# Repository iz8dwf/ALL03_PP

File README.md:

# ALL03_PP
Hi-Lo ALL-03 and MOD-EMUP programmers parallel port interface using the ATF-1502 CPLD.

This is a circuit that allows to use the Hi-Lo ALL-03 (and clones like the
MOD-EMUP) universal programmers/testers via the parallel port interface
using a patched DOSBOX. Original design by Nicola Di Lieto used an EPM7032
CPLD. I've used an ATF1502 CPLD that's still in production.

*** The JTAG port has a non-standard pinout *** 

The 2SB794 PNP darlington transistor can be substituted with a similar PNP
darlington. Using a normal PNP transistor with HFE < 200 makes this switching
voltage inverter misbehave. You can attempt to change the base resistor from
4k7 ohms to 2k2 ohms to make a lower HFE transistor work.

USE AT YOUR OWN RISK! 

PS: I believe a similar approach can be used also for the older CSA-0x ISA card based programmers (HI-LO EPP-0x and ALL-01 for example). Of course the adapter
board must be re-designed and a different patch needs to be created for dosbox. If you are interested (I still have an EPP-04, but I'm not going to use it anymore anytime soon) in such an adapter and want to help, contact me.

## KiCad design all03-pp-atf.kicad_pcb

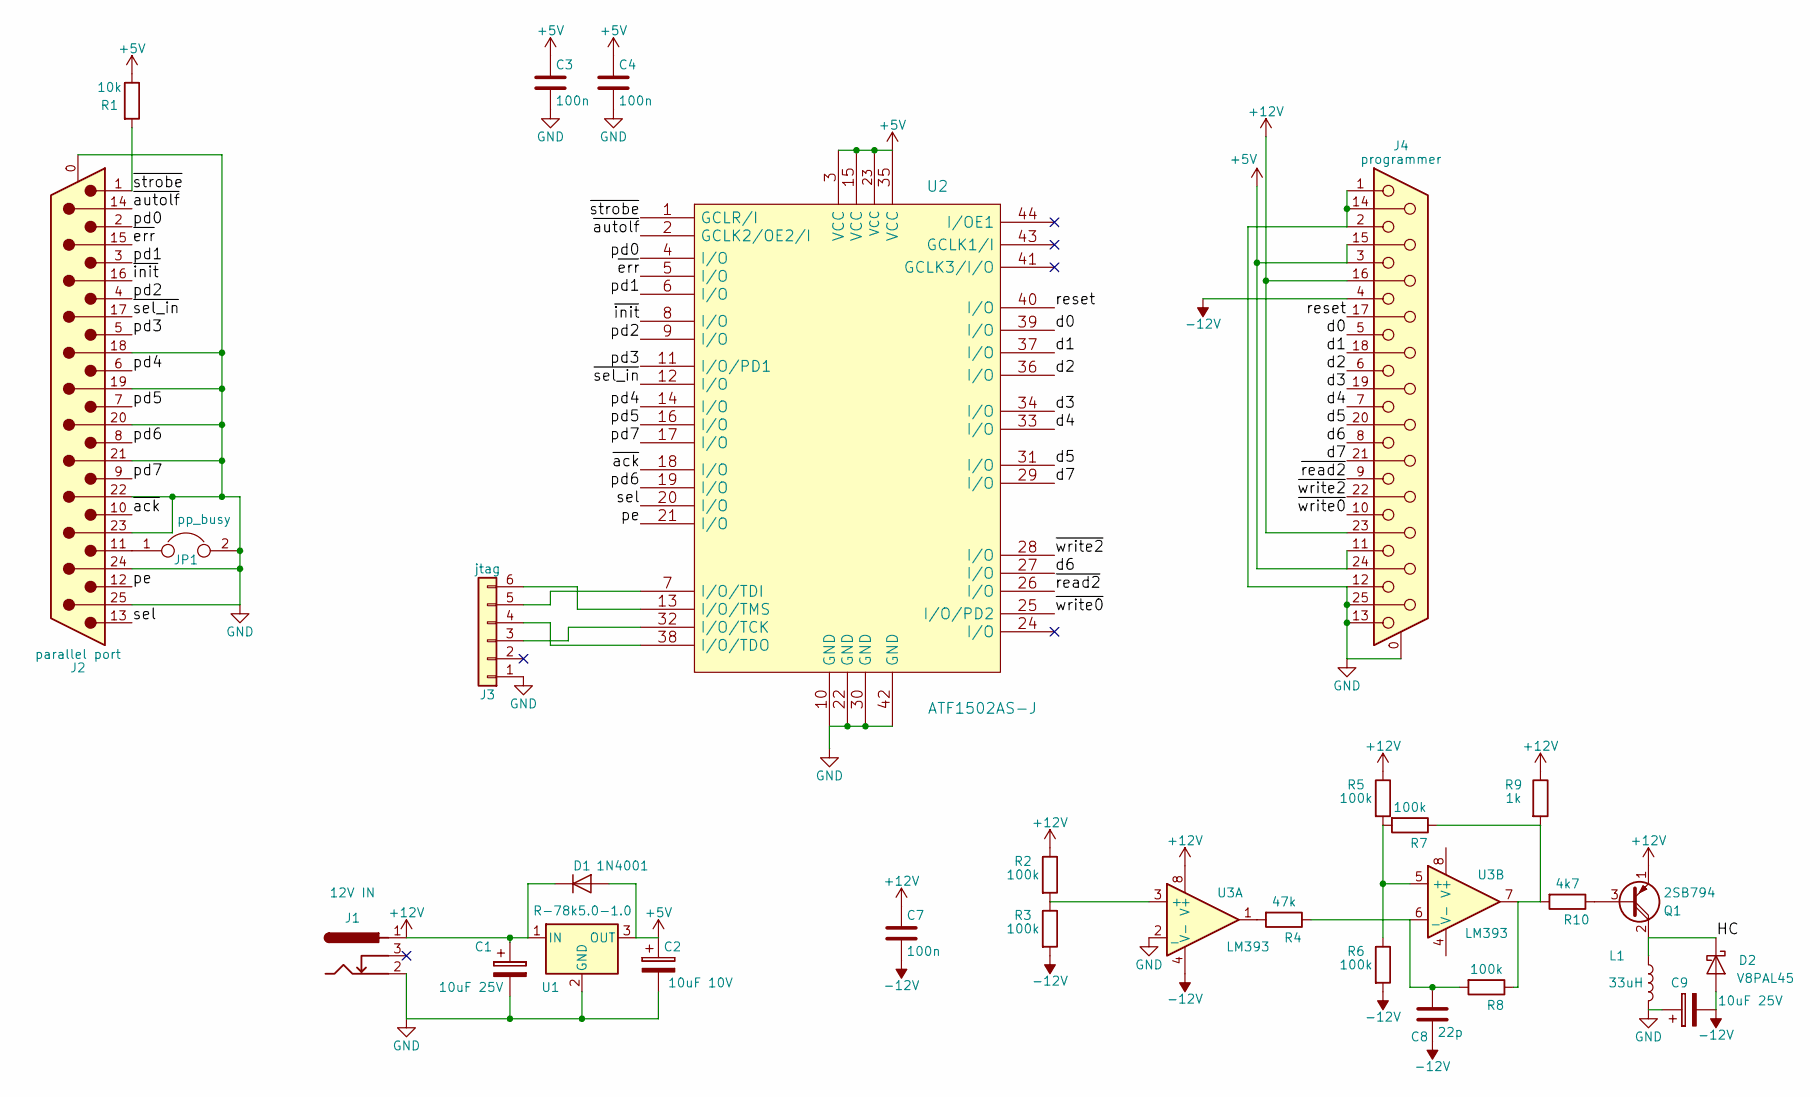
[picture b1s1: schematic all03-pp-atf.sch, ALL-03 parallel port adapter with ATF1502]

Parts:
C1, C9: 10uF 25V; CP_Radial_D5.0mm_P2.50mm
C2: 10uF 10V; CP_Radial_D5.0mm_P2.50mm
C3, C4: 100n; C_0805_HandSoldering
C7: 100n; C_Rect_L7.0mm_W2.5mm_P5.00mm
C8: 22p; C_Disc_D3.8mm_W2.6mm_P2.50mm
D1: 1N4001; D_DO-41_SOD81_P10.16mm_Horizontal
D2: V8PAL45; D_SMA-SMB_Universal_Handsoldering
J1: 12V IN; BARREL_JACK
J2: parallel port; DSUB-25_Male_Horizontal_Pitch2.77x2.84mm_EdgePinOffset4.94m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
J3: jtag; Pin_Header_Straight_1x06_Pitch2.54mm
J4: programmer; DSUB-25_Female_Horizontal_Pitch2.77x2.84mm_EdgePinOffset4.9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
JP1: pp_busy; R_1206_HandSoldering
L1: 33uH; L_Radial_D10.0mm_P5.00mm_Fastron_07P
Q1: 2SB794
R1: 10k; R_0805_HandSoldering
R2, R3, R5, R6, R7, R8: 100k; R_0805_HandSoldering
R4: 47k; R_0805_HandSoldering
R9: 1k; R_0805_HandSoldering
R10: 4k7; R_0805_HandSoldering
U1: R-78k5.0-1.0; TO-220-3_Vertical
U2: ATF1502AS-J; PLCC44
U3: LM393; DIP-8_W7.62mm_Socket

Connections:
+5V: C2.1, C3.1, C4.1, D1.2 (A), J4.3, J4.11, J4.15, J4.24, R1.1, U1.3 (OUT), U2.3 (VCC), U2.15 (VCC), U2.23 (VCC), U2.35 (VCC)
+12V: C1.1, C7.1, D1.1 (K), J1.1, J4.16, J4.23, Q1.1 (E), R2.1, R5.1, R9.1, U1.1 (IN), U3.8 (V+)
-12V: C7.2, C8.2, C9.2, D2.2 (A), J4.4, R3.2, R6.2, U3.4 (V-)
/HC: D2.1 (K), L1.1, Q1.2 (C)
/d0: J4.5, U2.39 (I/O)
/d1: J4.18, U2.37 (I/O)
/d2: J4.6, U2.36 (I/O)
/d3: J4.19, U2.34 (I/O)
/d4: J4.7, U2.33 (I/O)
/d5: J4.20, U2.31 (I/O)
/d6: J4.8, U2.27 (I/O)
/d7: J4.21, U2.29 (I/O)
/pd0: J2.2, U2.4 (I/O)
/pd1: J2.3, U2.6 (I/O)
/pd2: J2.4, U2.9 (I/O)
/pd3: J2.5, U2.11 (I/O/PD1)
/pd4: J2.6, U2.14 (I/O)
/pd5: J2.7, U2.16 (I/O)
/pd6: J2.8, U2.19 (I/O)
/pd7: J2.9, U2.17 (I/O)
/pe: J2.12, U2.21 (I/O)
/reset: J4.17, U2.40 (I/O)
/sel: J2.13, U2.20 (I/O)
/~ack: J2.10, U2.18 (I/O)
/~autolf: J2.14, U2.2 (GCLK2/OE2/I)
/~err: J2.15, U2.5 (I/O)
/~init: J2.16, U2.8 (I/O)
/~read2: J4.9, U2.26 (I/O)
/~sel_in: J2.17, U2.12 (I/O)
/~strobe: J2.1, R1.2, U2.1 (GCLR/I)
/~write0: J4.10, U2.25 (I/O/PD2)
/~write2: J4.22, U2.28 (I/O)
GND: C1.2, C2.2, C3.2, C4.2, C9.1, J1.2, J2.0 (PAD), J2.18, J2.19, J2.20, J2.21, J2.22, J2.23, J2.24, J2.25, J3.1, J4.0 (PAD), J4.1, J4.2, J4.12, J4.13, J4.14, J4.25, JP1.2, L1.2, U1.2 (GND), U2.10 (GND), U2.22 (GND), U2.30 (GND), U2.42 (GND), U3.2 (_)
unnamed: C8.1, R4.1, R8.2, U3.6 (_)
unnamed: J2.11, JP1.1
unnamed: J3.3, U2.32 (I/O/TCK)
unnamed: J3.4, U2.38 (I/O/TDO)
unnamed: J3.5, U2.7 (I/O/TDI)
unnamed: J3.6, U2.13 (I/O/TMS)
unnamed: Q1.3 (B), R10.1
unnamed: R2.2, R3.1, U3.3 (+)
unnamed: R4.2, U3.1
unnamed: R5.2, R6.1, R7.2, U3.5 (+)
unnamed: R7.1, R8.1, R9.2, R10.2, U3.7

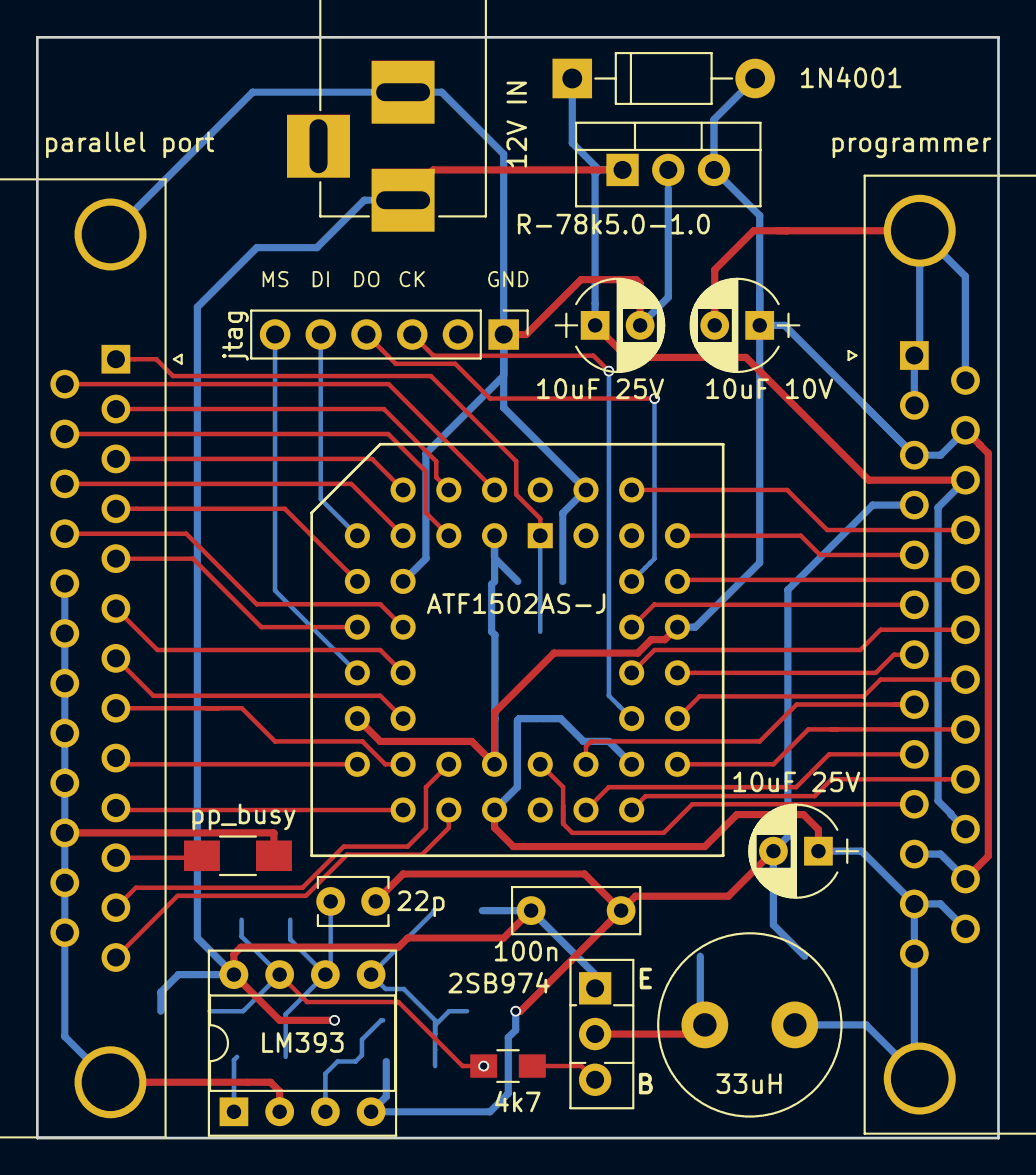
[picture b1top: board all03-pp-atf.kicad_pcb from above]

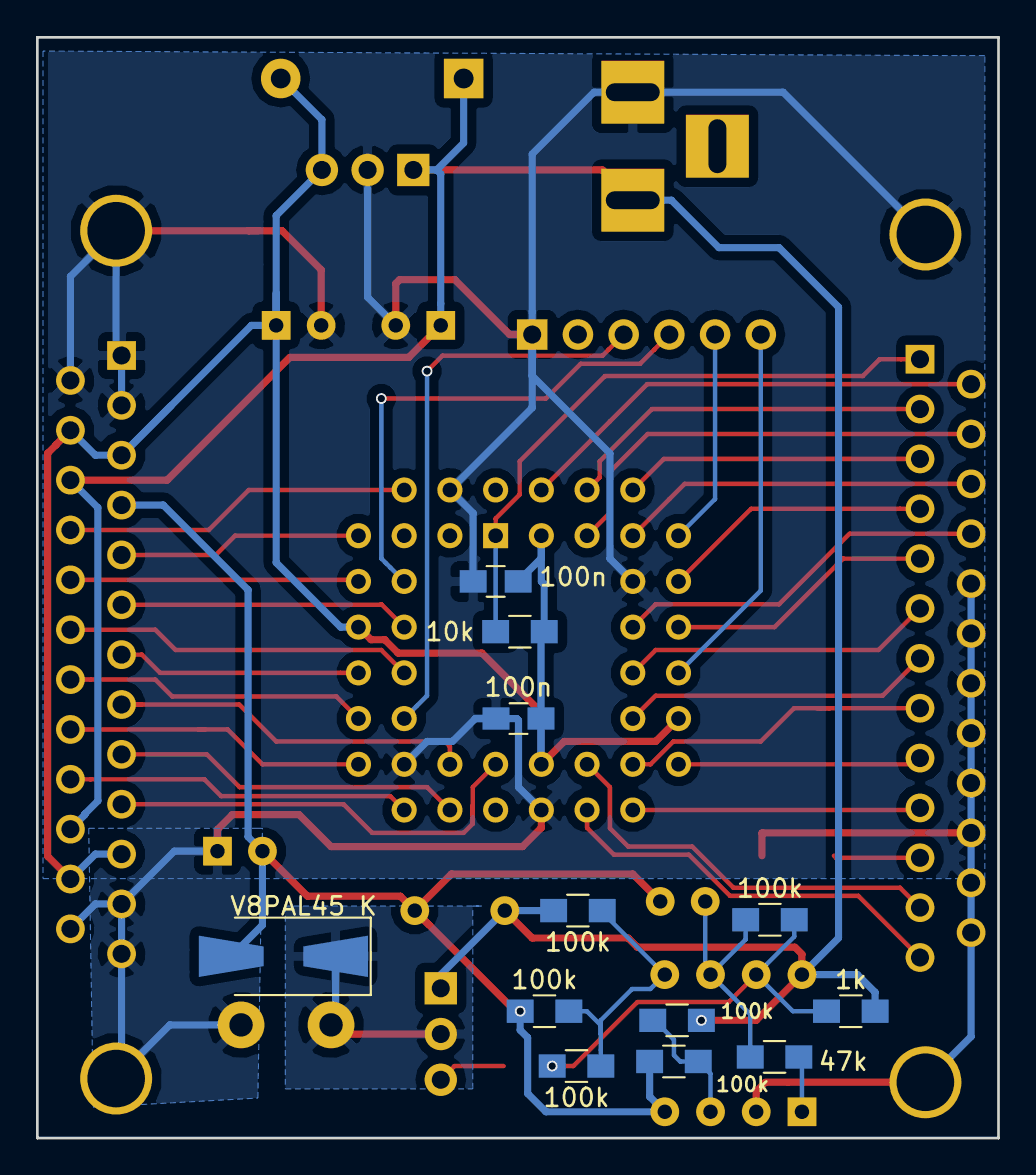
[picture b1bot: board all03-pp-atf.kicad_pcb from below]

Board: 2 copper layers, 53.4 x 61.1 mm, 29 parts (12 on the bottom side), 44 nets.

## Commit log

2023-12-09 Initial release
2023-12-09 removed unnecessary files
2023-12-14 removed unnecessary file
2023-12-14 better build instructions
2024-09-17 Added an image of the adapter
2024-09-17 better permissions
2025-06-20 readme mod
